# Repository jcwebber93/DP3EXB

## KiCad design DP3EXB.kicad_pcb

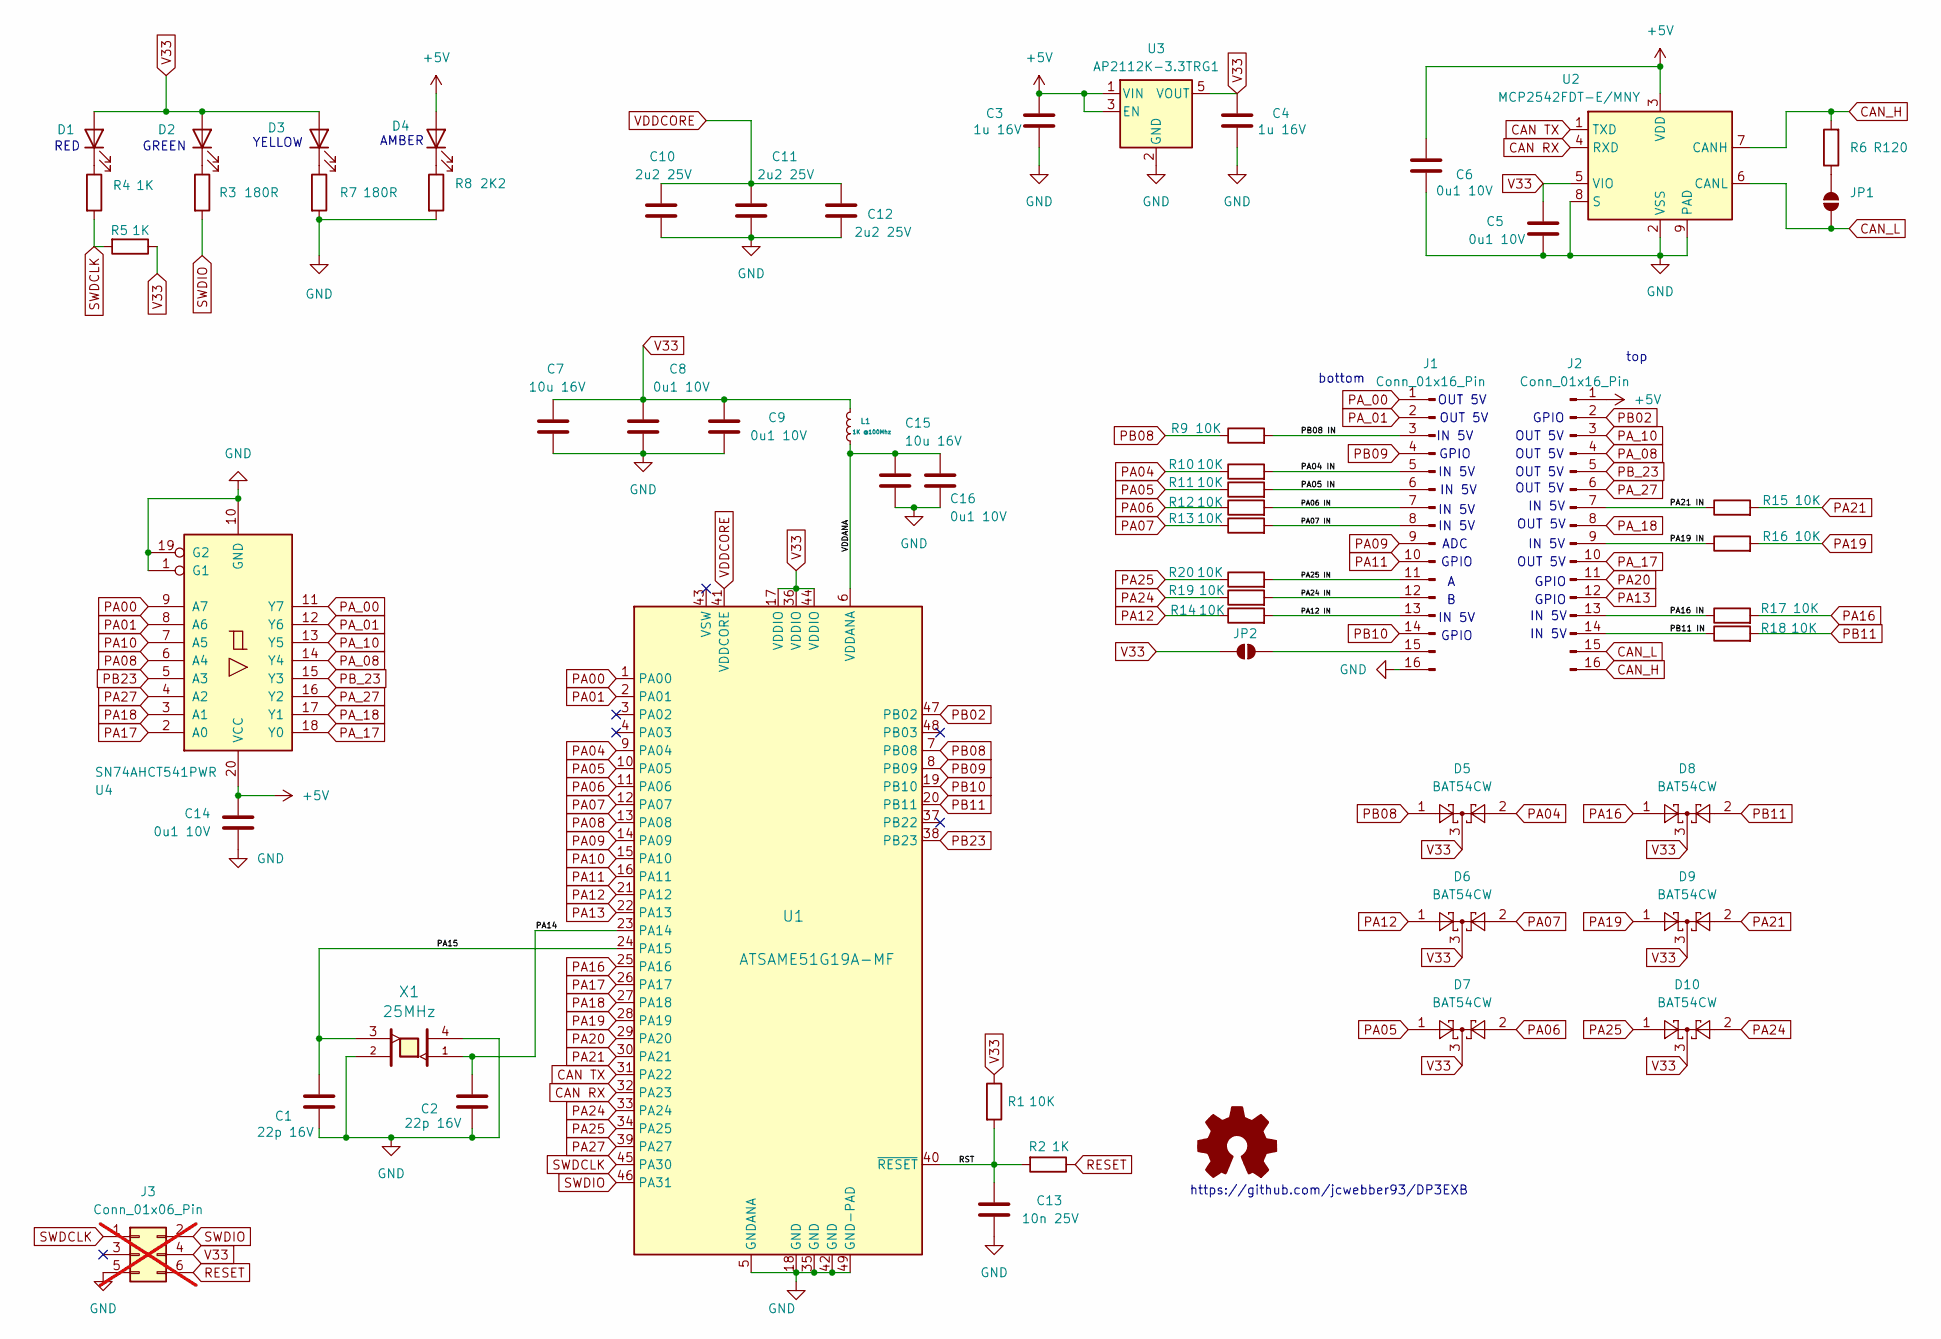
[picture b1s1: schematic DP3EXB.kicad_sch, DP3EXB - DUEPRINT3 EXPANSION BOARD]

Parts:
C1, C2: 22p 16V; C_0402_1005Metric; Part Number C0402C220J4GACTU; LCSC Part # C2168192
C3, C4: 1u 16V; C_0603_1608Metric; Part Number CL10B105KO8NNNC; LCSC Part # C59782
C5, C6, C8, C9, C14, C16: 0u1 10V; C_0402_1005Metric; Part Number CL05B104KP5NNNC; LCSC Part # C285038
C7, C15: 10u 16V; C_0805_2012Metric; Part Number CL21B106KOQNNNE; LCSC Part # C95841
C10, C11, C12: 2u2 25V; C_0402_1005Metric; Part Number GRM1555C1E2R2BA01D; LCSC Part # C3867810
C13: 10n 25V; C_0402_1005Metric; Part Number CL05B103KA5VPNC; LCSC Part # C284987
D1: 150040RS73240; LED_0402_1005Metric; Part Number 150040RS73240; LCSC Part # C364556
D2: 150040VS73240; LED_0402_1005Metric; Part Number 150040VS73240; LCSC Part # C273602
D3: 150040YS73240; LED_0402_1005Metric; Part Number 150040YS73240; LCSC Part # C273600
D4: 150040AS73220; LED_0402_1005Metric; Part Number 150040AS73220; LCSC Part # C273599
D5, D6, D7, D8, D9, D10: BAT54CW; SOT-323_SC-70; LCSC Part # C22392482
J1, J2: Conn_01x16_Pin; PinHeader_1x16_P2.54mm_Vertical
J3: Conn_01x06_Pin; PinHeader_2x03_P1.27mm_Vertical; not fitted
JP1, JP2: SolderJumper_2_Open; SolderJumper-2_P1.3mm_Open_TrianglePad1.0x1.5mm
L1: 1K @100Mhz; L_0603_1608Metric; Part Number 742792662 or PE-0603FB102ST or similar; LCSC Part # C85824
R1, R9, R10, R11, R12, R13, R14, R15, R16, R17, R18, R19, R20: 10K; R_0402_1005Metric; Part Number RK73H1ETTP1002F; LCSC Part # C131361
R2, R4, R5: 1K; R_0402_1005Metric; Part Number RMCF0402FT1K00; LCSC Part # C2479070
R3, R7: 180R; R_0402_1005Metric; Part Number RMCF0402FT180R; LCSC Part # C138045
R6: R120; R_0603_1608Metric; LCSC Part # C114640
R8: 2K2; R_0402_1005Metric; Part Number RK73H1ETTP2201F; LCSC Part # C413087
U1: ATSAME51G19A-MF; QFN-48-1EP_7x7mm_P0.5mm_EP5.2x5.2mm_ThermalVias; Part Number ATSAME51G19A-MF; LCSC Part # C614482
U2: MCP2542FDT-E/MNY; DFN-8-1EP_3x2mm_P0.5mm_EP1.3x1.5mm; Part Number MCP2542FDT-E/MNY; LCSC Part # C114028
U3: AP2112K-3.3TRG1; SOT-23-5; Part Number AP2112K-3.3TRG1; LCSC Part # C51118
U4: SN74AHCT541PWR; TSSOP-20_4.4x6.5mm_P0.65mm; Part Number SN74AHCT541PWR; LCSC Part # C50989
X1: TSX-3225 25.0000MF10P-C; Crystal_SMD_ECS-33B-4Pin_3.2x2.5mm; Part Number TSX-3225 25.0000MF10P-C; LCSC Part # C6190583

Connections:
+5V: C3.1, C6.1, C14.2, D4.2 (A), J2.1, U2.3 (VDD), U3.1 (VIN), U3.3 (EN), U4.20 (VCC)
/PA04 IN: J1.5, R10.2
/PA05 IN: J1.6, R11.2
/PA06 IN: J1.7, R12.2
/PA07 IN: J1.8, R13.2
/PA12 IN: J1.13, R14.2
/PA14: C2.1, U1.23 (PA14), X1.1
/PA15: C1.1, U1.24 (PA15), X1.3
/PA16 IN: J2.13, R17.1
/PA19 IN: J2.9, R16.1
/PA21 IN: J2.7, R15.1
/PA24 IN: J1.12, R19.2
/PA25 IN: J1.11, R20.2
/PB08 IN: J1.3, R9.2
/PB11 IN: J2.14, R18.1
/RST: C13.1, R1.2, R2.2, U1.40 (~RESET)
/VDDANA: C15.1, C16.1, L1.2, U1.6 (VDDANA)
CAN RX: U1.32 (PA23), U2.4 (RXD)
CAN TX: U1.31 (PA22), U2.1 (TXD)
CAN_H: J2.16, R6.2, U2.7 (CANH)
CAN_L: J2.15, JP1.1 (A), U2.6 (CANL)
GND: C1.2, C2.2, C3.2, C4.2, C5.2, C6.2, C7.2, C8.2, C9.2, C10.2, C11.2, C12.2, C13.2, C14.1, C15.2, C16.2, J1.16, J3.5, R7.2, R8.2, U1.5 (GNDANA), U1.18 (GND), U1.35 (GND), U1.42 (GND), U1.49 (GND-PAD), U2.2 (VSS), U2.8 (S), U2.9 (PAD), U3.2 (GND), U4.1 (G1), U4.10 (GND), U4.19 (G2), X1.2, X1.4
unnamed: D1.1 (K), R4.1
unnamed: D2.1 (K), R3.1
unnamed: D3.1 (K), R7.1
unnamed: D4.1 (K), R8.1
unnamed: J1.15, JP2.1 (A)
unnamed: JP1.2 (B), R6.1
PA00: U1.1 (PA00), U4.9 (A7)
PA01: U1.2 (PA01), U4.8 (A6)
PA04: D5.2, R10.1, U1.9 (PA04)
PA05: D7.1, R11.1, U1.10 (PA05)
PA06: D7.2, R12.1, U1.11 (PA06)
PA07: D6.2, R13.1, U1.12 (PA07)
PA08: U1.13 (PA08), U4.6 (A4)
PA09: J1.9, U1.14 (PA09)
PA10: U1.15 (PA10), U4.7 (A5)
PA11: J1.10, U1.16 (PA11)
PA12: D6.1, R14.1, U1.21 (PA12)
PA13: J2.12, U1.22 (PA13)
PA16: D8.1, R17.2, U1.25 (PA16)
PA17: U1.26 (PA17), U4.2 (A0)
PA18: U1.27 (PA18), U4.3 (A1)
PA19: D9.1, R16.2, U1.28 (PA19)
PA20: J2.11, U1.29 (PA20)
PA21: D9.2, R15.2, U1.30 (PA21)
PA24: D10.2, R19.1, U1.33 (PA24)
PA25: D10.1, R20.1, U1.34 (PA25)
PA27: U1.39 (PA27), U4.4 (A2)
PA_00: J1.1, U4.11 (Y7)
PA_01: J1.2, U4.12 (Y6)
PA_08: J2.4, U4.14 (Y4)
PA_10: J2.3, U4.13 (Y5)
PA_17: J2.10, U4.18 (Y0)
PA_18: J2.8, U4.17 (Y1)
PA_27: J2.6, U4.16 (Y2)
PB02: J2.2, U1.47 (PB02)
PB08: D5.1, R9.1, U1.7 (PB08)
PB09: J1.4, U1.8 (PB09)
PB10: J1.14, U1.19 (PB10)
PB11: D8.2, R18.2, U1.20 (PB11)
PB23: U1.38 (PB23), U4.5 (A3)
PB_23: J2.5, U4.15 (Y3)
RESET: J3.6, R2.1
SWDCLK: J3.1, R4.2, R5.2, U1.45 (PA30)
SWDIO: J3.2, R3.2, U1.46 (PA31)
V33: C4.1, C5.1, C7.1, C8.1, C9.1, D1.2 (A), D2.2 (A), D3.2 (A), D5.3, D6.3, D7.3, D8.3, D9.3, D10.3, J3.4, JP2.2 (B), L1.1, R1.1, R5.1, U1.17 (VDDIO), U1.36 (VDDIO), U1.44 (VDDIO), U2.5 (VIO), U3.5 (VOUT)
VDDCORE: C10.1, C11.1, C12.1, U1.41 (VDDCORE)

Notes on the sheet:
GPIO
IN 5V
OUT 5V
bottom
ADC
GREEN
AMBER
https://github.com/jcwebber93/DP3EXB
RED
top
YELLOW

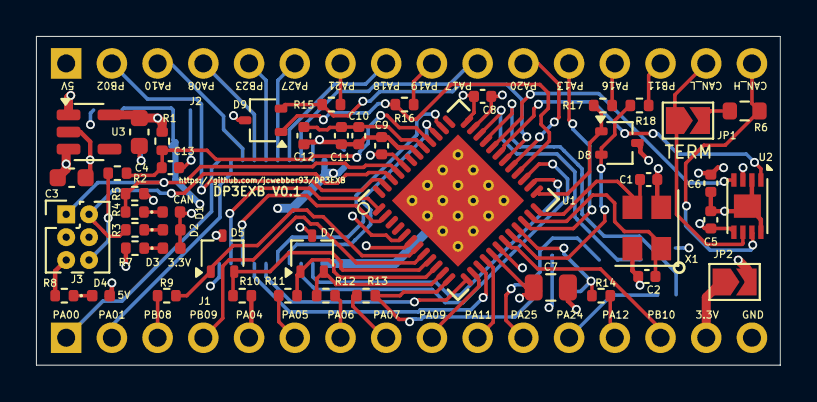
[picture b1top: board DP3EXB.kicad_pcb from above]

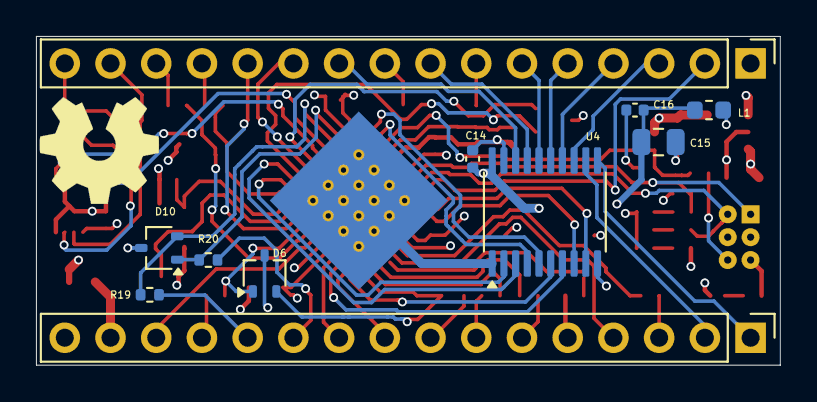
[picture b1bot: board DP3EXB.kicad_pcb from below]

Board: 4 copper layers, 41.3 x 18.3 mm, 57 parts (11 on the bottom side), 68 nets.

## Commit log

2026-05-25 Initial Push
    DuePrint3 Expansion Board for Stratasys conversions. Replaces the SammyC21 + STM32 Blackpill.
2026-06-04 Minor updates
    Minor updates
2026-06-04 Minor updated
    Minor updated
